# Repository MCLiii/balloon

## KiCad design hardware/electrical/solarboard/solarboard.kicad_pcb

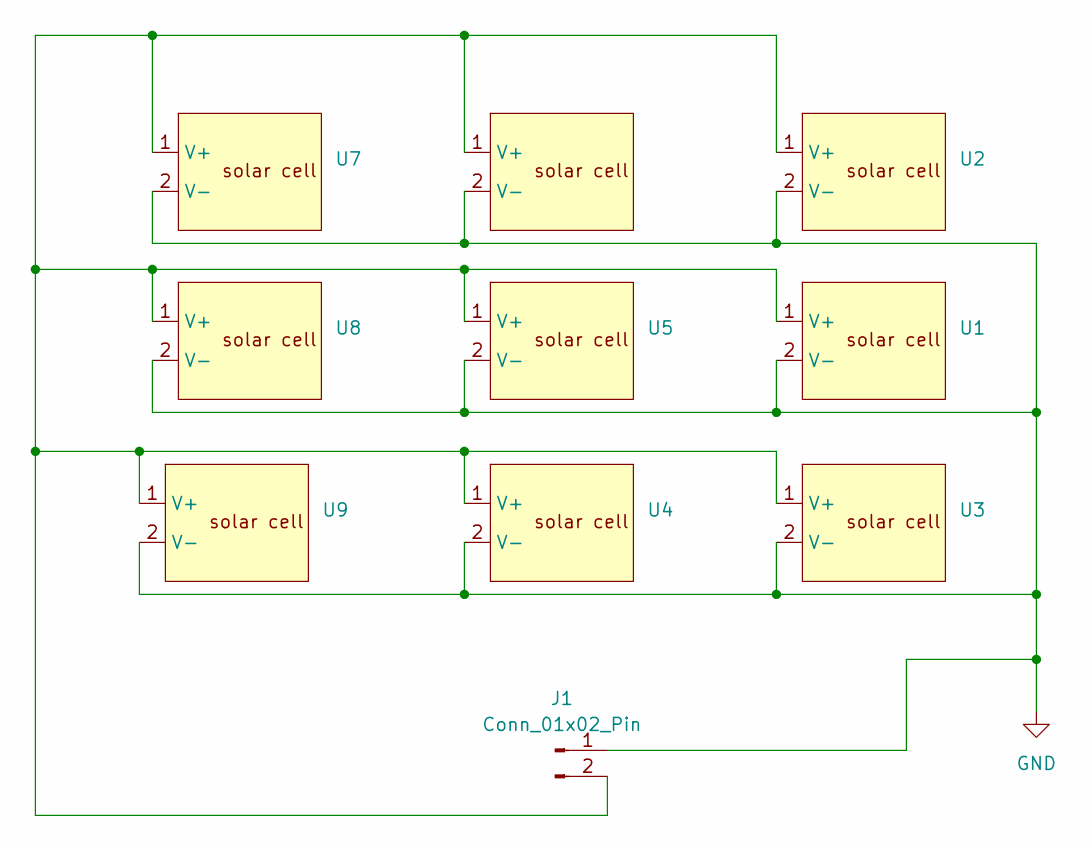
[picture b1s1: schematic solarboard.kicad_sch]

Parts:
J1: Conn_01x02_Pin; PinHeader_1x02_P1.00mm_Horizontal
U1, U2, U3, U4, U5, U6, U7, U8, U9: Solar_Pannel_holes

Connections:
GND: J1.1, U1.2 (V-), U2.2 (V-), U3.2 (V-), U4.2 (V-), U5.2 (V-), U6.2 (V-), U7.2 (V-), U8.2 (V-), U9.2 (V-)
unnamed: J1.2, U1.1 (V+), U2.1 (V+), U3.1 (V+), U4.1 (V+), U5.1 (V+), U6.1 (V+), U7.1 (V+), U8.1 (V+), U9.1 (V+)

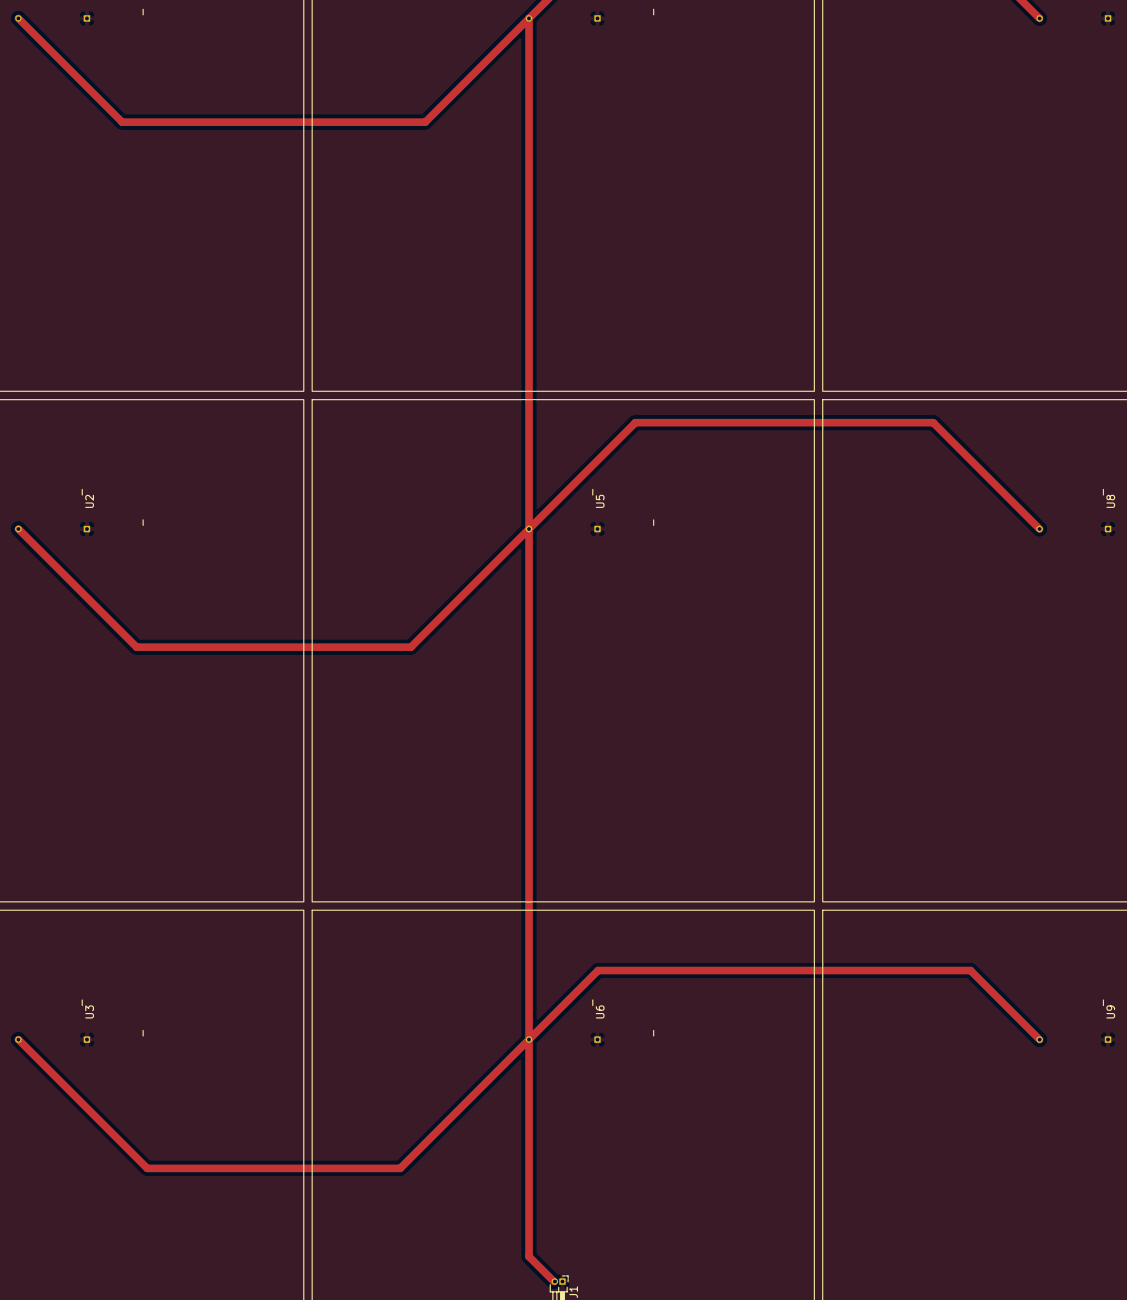
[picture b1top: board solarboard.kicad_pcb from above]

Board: 2 copper layers, 10 parts (0 on the bottom side), 2 nets.

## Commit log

2025-09-01 Add hardware design files
2025-09-04 solar board v0.1
2025-09-06 software inital commit
2025-09-06 pygame mod
2025-09-11 revision solar board
2025-09-13 Balloon software
2025-09-13 telemetry dashboard
2025-09-14 Add i2c firmware
2025-09-14 Maybe remove the microcontroller and i2c everything?
2025-09-14 vibe code a little i2c reader
2025-09-14 add mod.rs
2025-09-15 seeed xiao i2c slave
2025-09-15 working pressure sensor driver
2025-09-15 IMU sensor driver
2025-09-18 update designs and firmware
2025-09-18 update telemetry
2025-09-19 Remove barometer because it fucked up my i2c
2025-09-19 update telemetry dashboard to use real data
2025-09-19 add db inserts
